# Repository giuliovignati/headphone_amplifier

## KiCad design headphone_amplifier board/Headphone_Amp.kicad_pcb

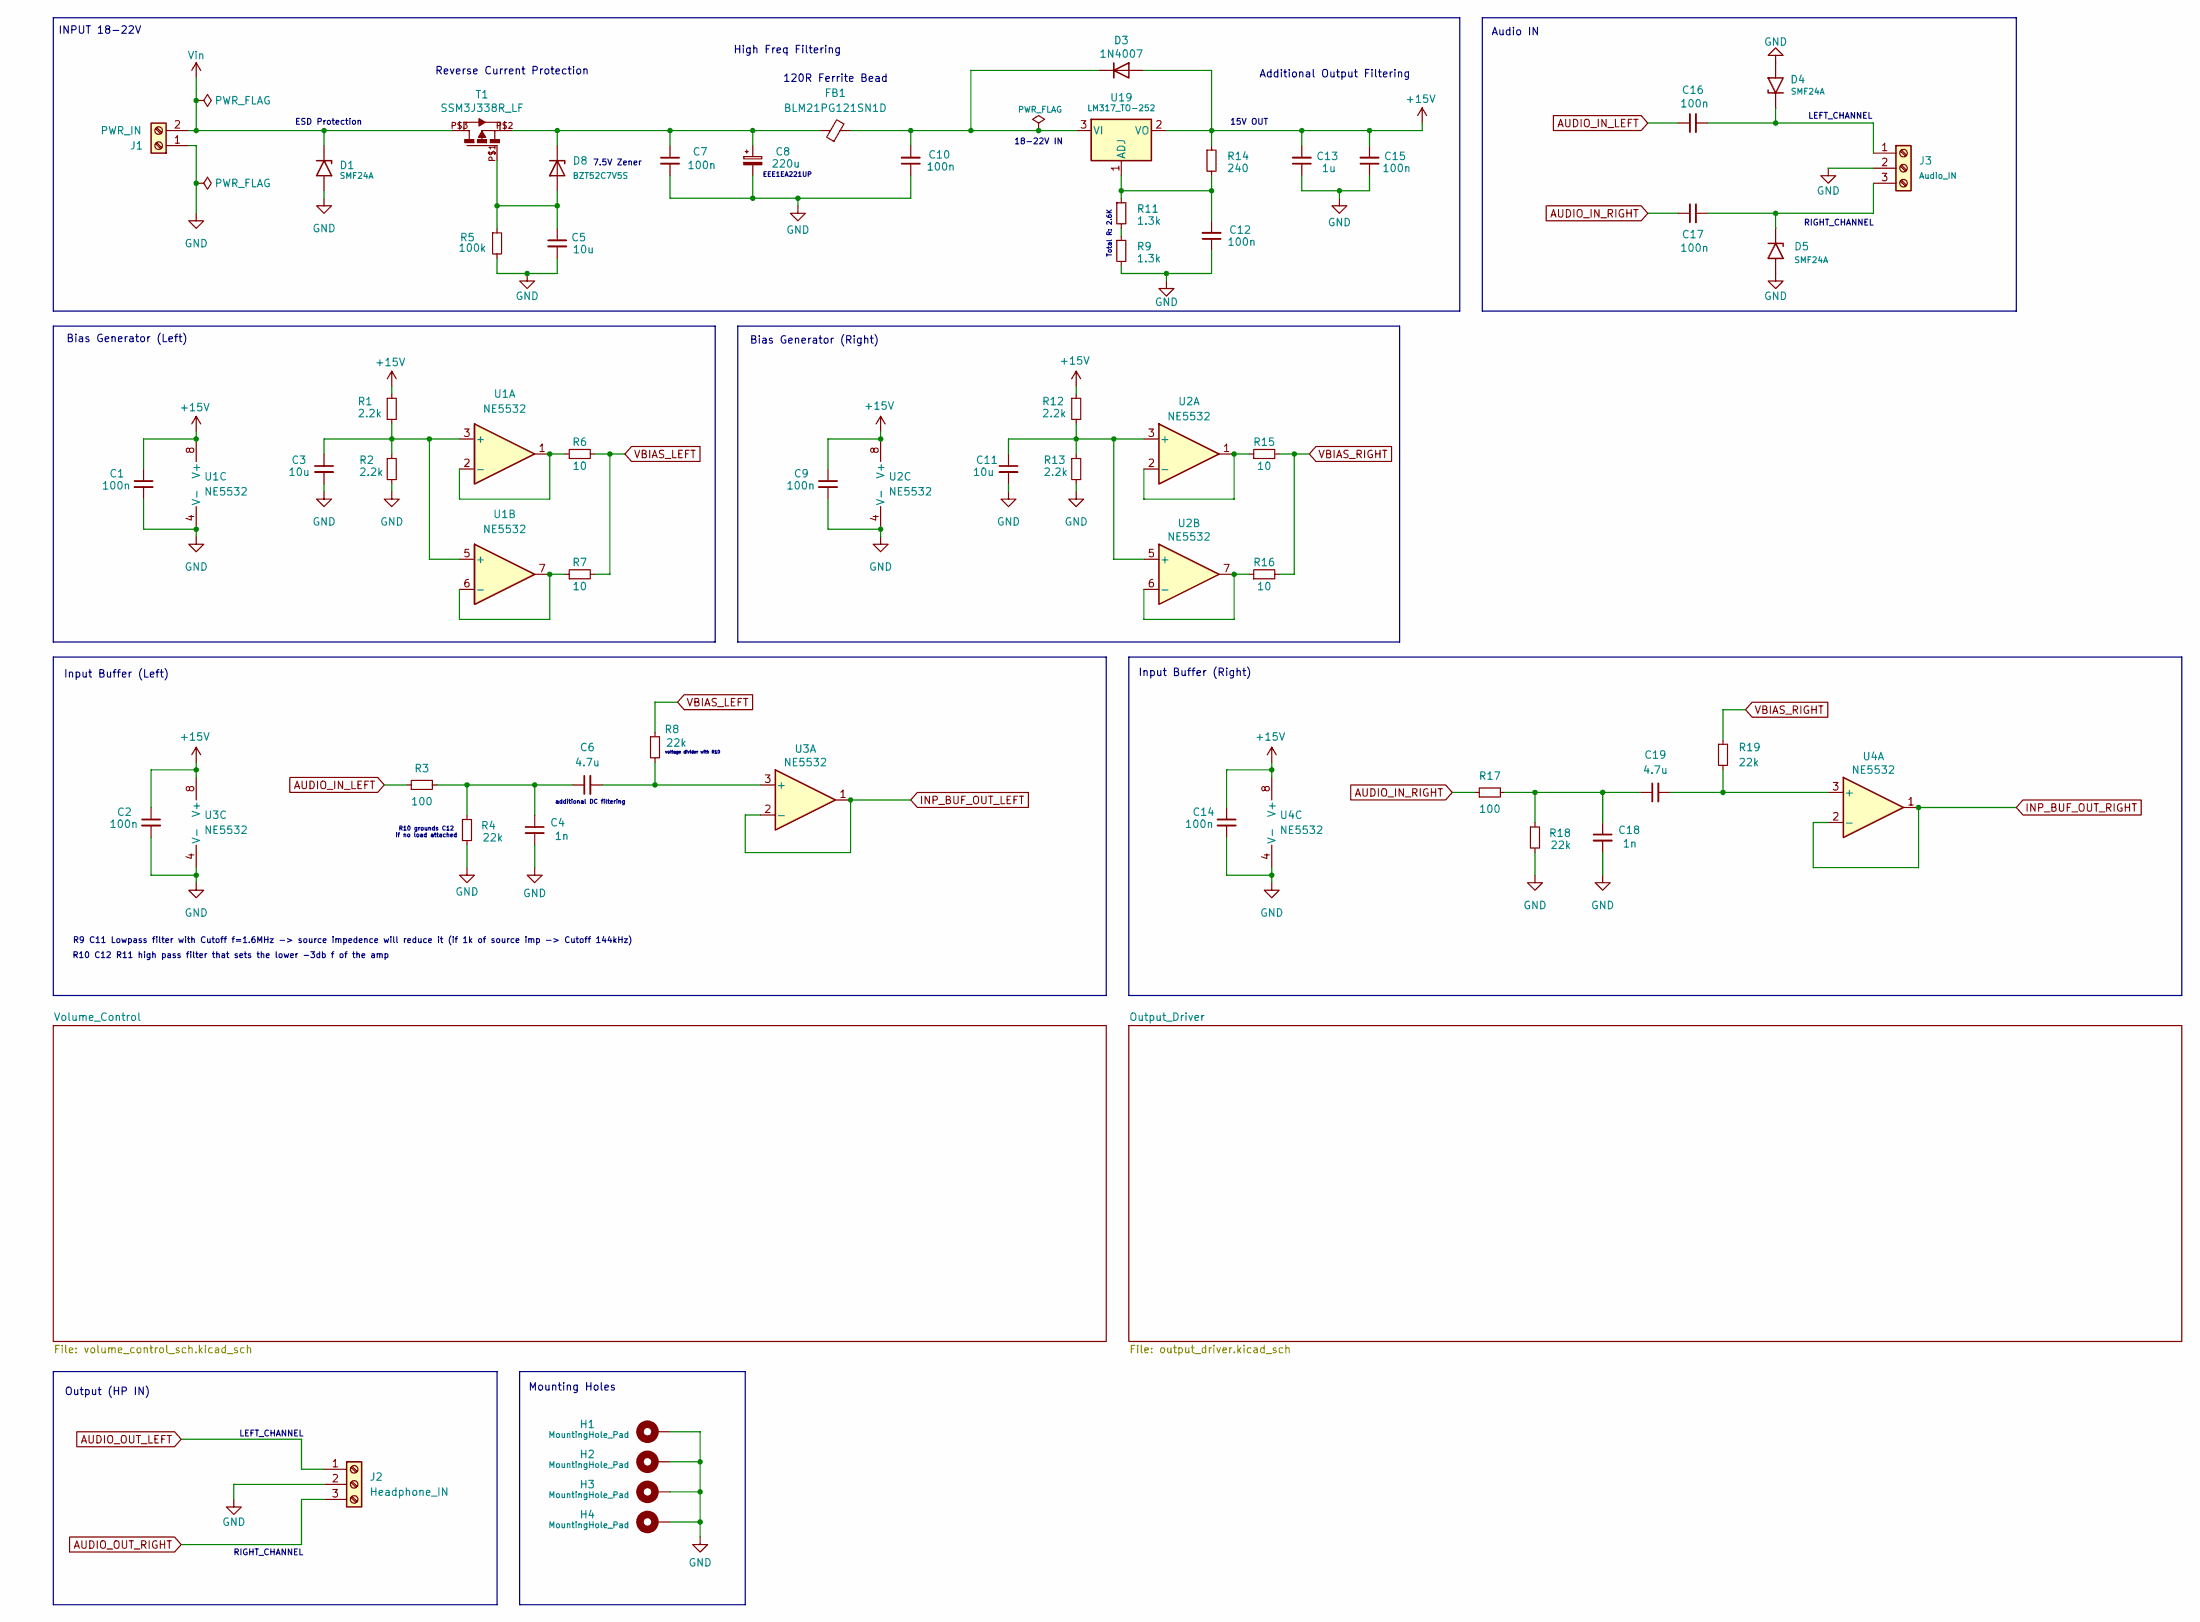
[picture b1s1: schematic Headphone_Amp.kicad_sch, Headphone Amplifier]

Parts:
C1, C2, C7, C9, C10, C12, C14, C15, C16, C17: 100n; C_0805_2012Metric_Pad1.18x1.45mm_HandSolder
C3, C5, C11: 10u; C_0805_2012Metric_Pad1.18x1.45mm_HandSolder
C4, C18: 1n; C_0805_2012Metric_Pad1.18x1.45mm_HandSolder
C6, C19: 4.7u; C_0805_2012Metric_Pad1.18x1.45mm_HandSolder
C8: 220u; EEE1EA221UP
C13: 1u; C_0805_2012Metric_Pad1.18x1.45mm_HandSolder
D1, D4, D5: SMF24A; D_SOD-123
D3: 1N4007; D_SMA
D8: BZT52C7V5S; D_SOD-123F
FB1: BLM21PG121SN1D; C_0805_2012Metric_Pad1.18x1.45mm_HandSolder
H1, H2, H3, H4: MountingHole_Pad; MountingHole_3.2mm_M3_Pad_Via
J1: PWR_IN; TerminalBlock_bornier-2_P5.08mm
J2: Headphone_IN; TerminalBlock_bornier-3_P5.08mm
J3: Audio_IN; TerminalBlock_bornier-3_P5.08mm
R1, R2, R12, R13: 2.2k; R_0805_2012Metric_Pad1.20x1.40mm_HandSolder
R3, R17: 100; R_0805_2012Metric_Pad1.20x1.40mm_HandSolder
R4, R8, R18, R19: 22k; R_0805_2012Metric_Pad1.20x1.40mm_HandSolder
R5: 100k; R_0805_2012Metric_Pad1.20x1.40mm_HandSolder
R6, R7, R15, R16: 10; R_0805_2012Metric_Pad1.20x1.40mm_HandSolder
R9, R11: 1.3k; R_0805_2012Metric_Pad1.20x1.40mm_HandSolder
R14: 240; R_0805_2012Metric_Pad1.20x1.40mm_HandSolder
T1: SSM3J338R_LF
U1, U2, U3, U4: NE5532; SOIC-8_3.9x4.9mm_P1.27mm
U19: LM317_TO-252; SOT-223

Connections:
+15V: C1.1, C2.1, C9.1, C13.2, C14.1, C15.2, D3.2 (A), R1.1, R12.1, R14.1, U1.8 (V+), U2.8 (V+), U3.8 (V+), U4.8 (V+), U19.2 (VO); also elsewhere on the board
AUDIO_IN_LEFT: C16.1, R3.1
AUDIO_IN_RIGHT: C17.1, R17.1
AUDIO_OUT_LEFT: J2.1; also elsewhere on the board
AUDIO_OUT_RIGHT: J2.3; also elsewhere on the board
GND: C1.2, C2.2, C3.2, C4.2, C5.2, C7.2, C8.2, C9.2, C10.1, C11.2, C12.1, C13.1, C14.2, C15.1, C18.2, D1.2 (A2), D4.2 (A2), D5.2 (A2), H1.1, H2.1, H3.1, H4.1, J1.1, J2.2, J3.2, R2.2, R4.2, R5.2, R9.2, R13.2, R18.2, U1.4 (V-), U2.4 (V-), U3.4 (V-), U4.4 (V-); also elsewhere on the board
INP_BUF_OUT_LEFT: U3.1, U3.2 (-); also elsewhere on the board
INP_BUF_OUT_RIGHT: U4.1, U4.2 (-); also elsewhere on the board
unnamed: C4.1, C6.1, R3.2, R4.1
unnamed: C18.1, C19.1, R17.2, R18.1
unnamed: C10.2, D3.1 (K), FB1.2, U19.3 (VI)
unnamed: C16.2, D4.1 (A1), J3.1
unnamed: C17.2, D5.1 (A1), J3.3
unnamed: C5.1, D8.2 (A), R5.1, T1.P$1
unnamed: C7.1, C8.1, D8.1 (K), FB1.1, T1.P$2
unnamed: R9.1, R11.2
unnamed: C3.1, R1.2, R2.1, U1.3 (+), U1.5 (+)
unnamed: R6.1, U1.1, U1.2 (-)
unnamed: R7.1, U1.6 (-), U1.7
unnamed: C11.1, R12.2, R13.1, U2.3 (+), U2.5 (+)
unnamed: R15.1, U2.1, U2.2 (-)
unnamed: R16.1, U2.6 (-), U2.7
unnamed: C6.2, R8.2, U3.3 (+)
unnamed: C19.2, R19.2, U4.3 (+)
unnamed: C12.2, R11.1, R14.2, U19.1 (ADJ)
VBIAS_LEFT: R6.2, R7.2, R8.1; also elsewhere on the board
VBIAS_RIGHT: R15.2, R16.2, R19.1; also elsewhere on the board
Vin: D1.1 (A1), J1.2, T1.P$3

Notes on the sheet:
Audio IN
120R Ferrite Bead
15V OUT
ESD Protection
7.5V Zener
R10 C12 R11 high pass filter that sets the lower -3db f of the amp
Total R: 2.6K
Bias Generator (Right)
Mounting Holes
Input Buffer (Right)
High Freq Filtering
Output (HP IN)
EEE1EA221UP
Reverse Current Protection
RIGHT_CHANNEL
Bias Generator (Left)
LEFT_CHANNEL
INPUT 18-22V
R10 grounds C12 if no load attached
18-22V IN
Additional Output Filtering
R9 C11 Lowpass filter with Cutoff f=1.6MHz -> source impedence will reduce it (if 1k of source imp -> Cutoff 144kHz)
Input Buffer (Left)
voltage divider with R10
additional DC filtering

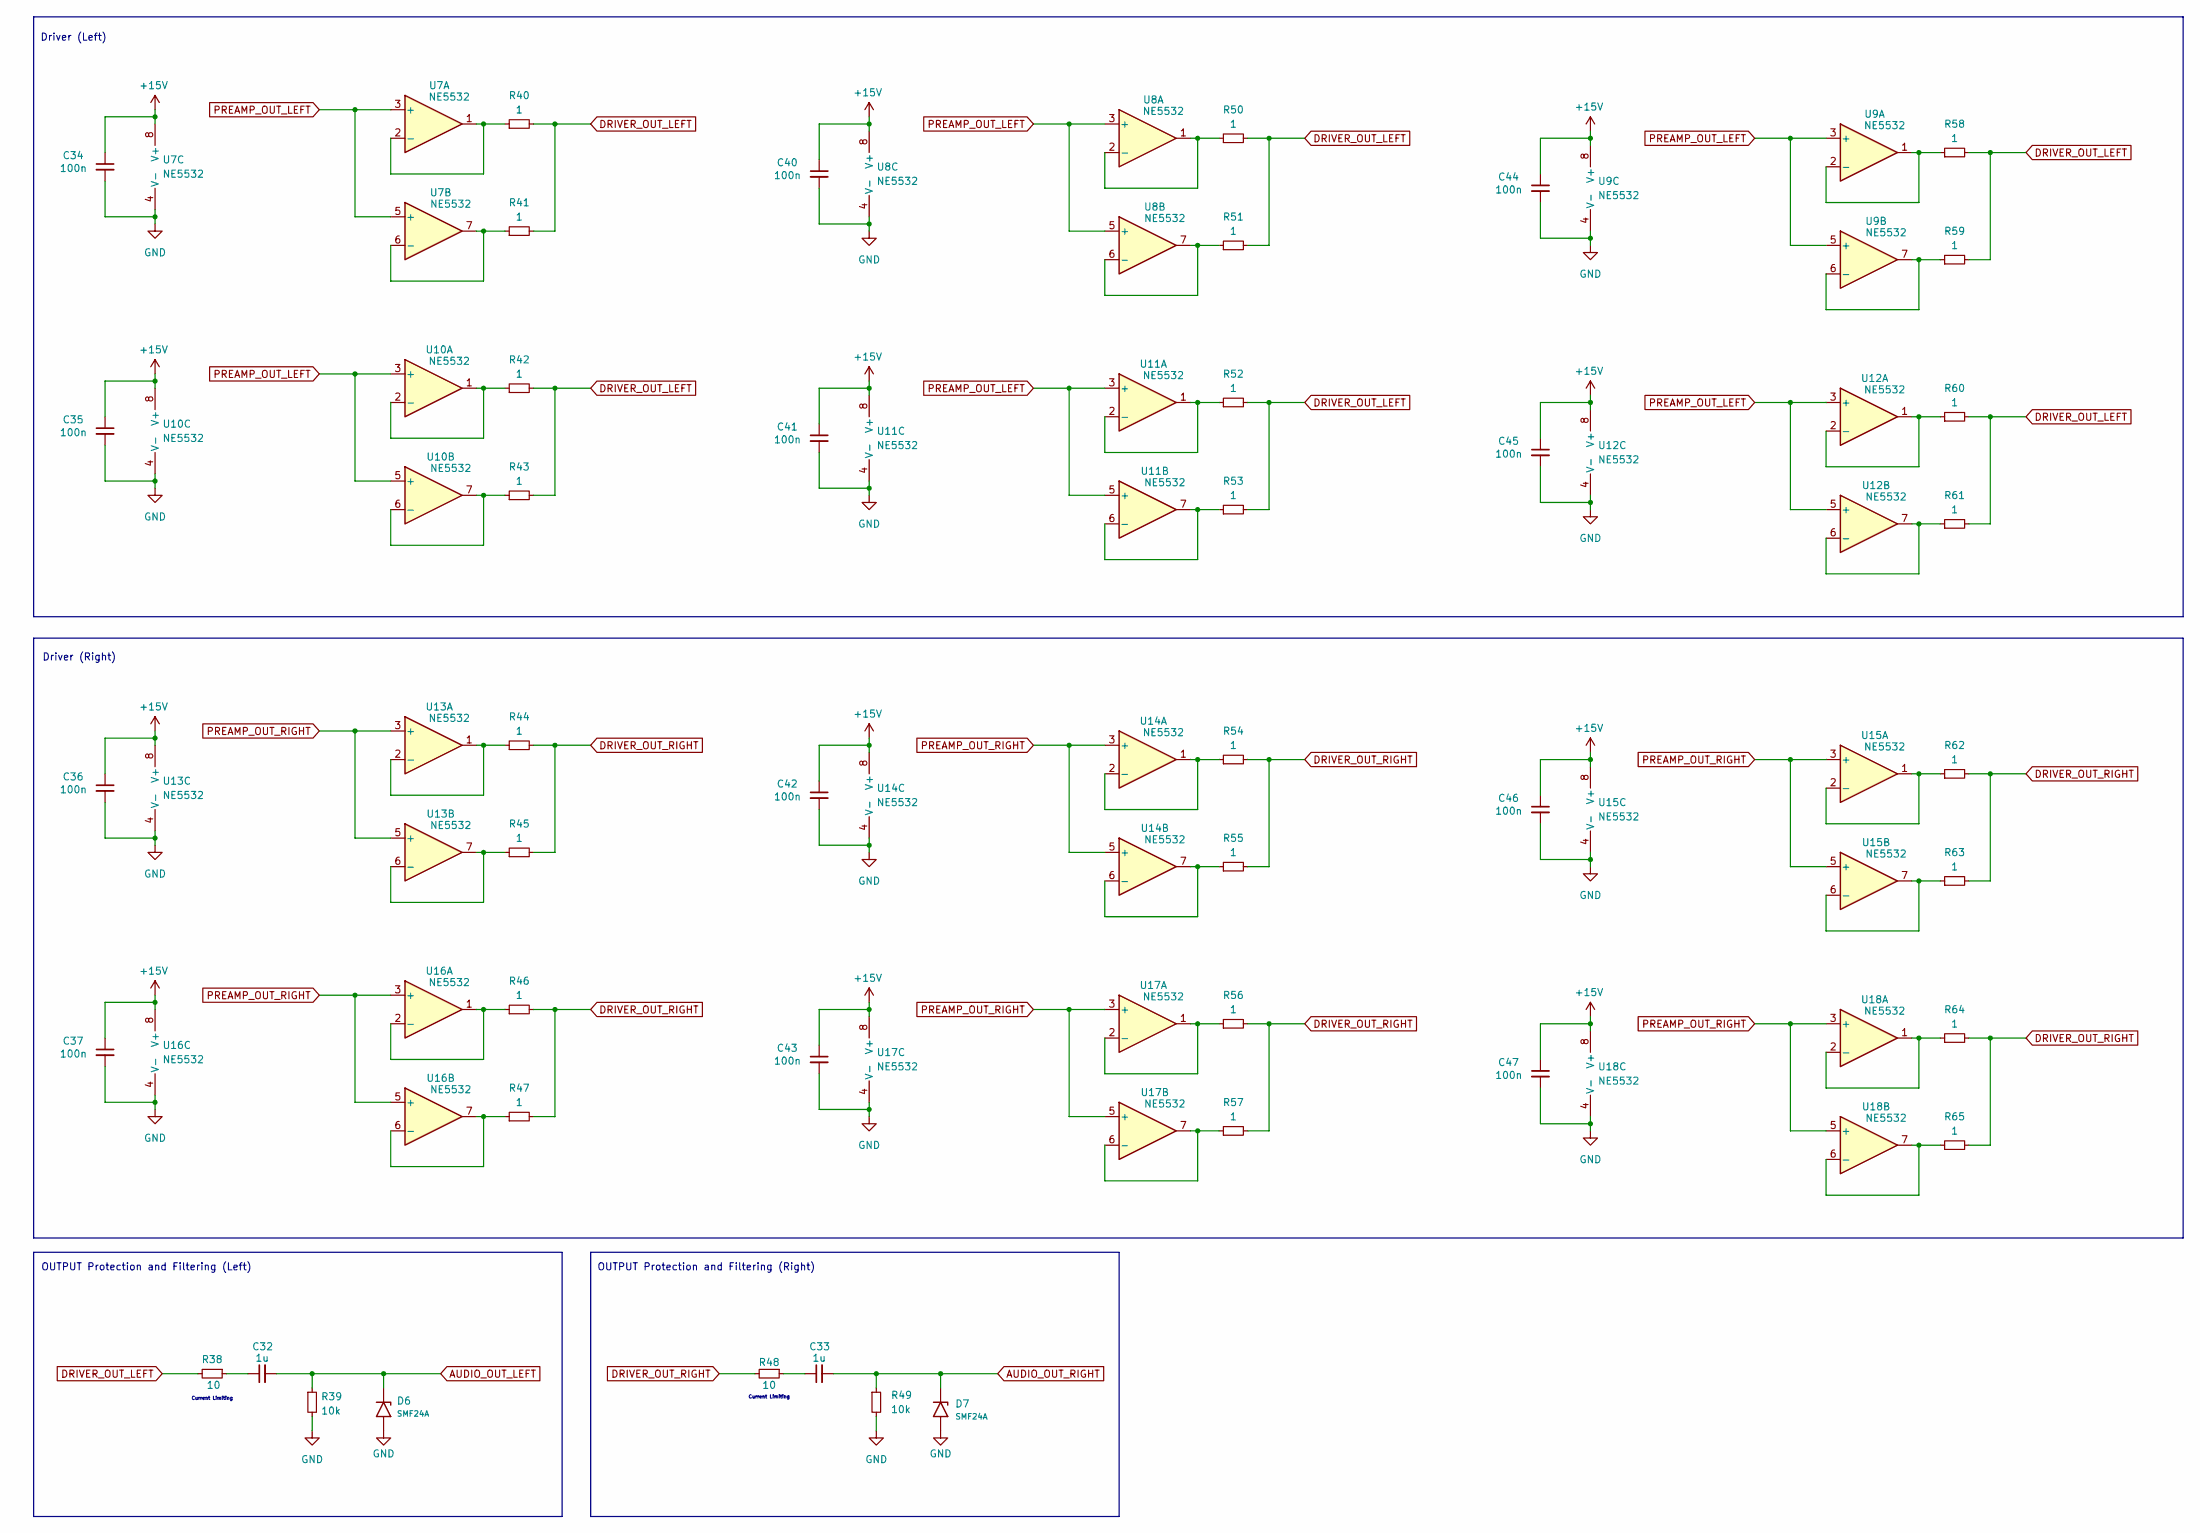
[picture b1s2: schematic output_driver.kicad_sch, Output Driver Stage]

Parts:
C32, C33: 1u; C_Rect_L18.0mm_W7.0mm_P15.00mm_FKS3_FKP3
C34, C35, C36, C37, C40, C41, C42, C43, C44, C45, C46, C47: 100n; C_0805_2012Metric_Pad1.18x1.45mm_HandSolder
D6, D7: SMF24A; D_SOD-123
R38, R48: 10; R_0805_2012Metric_Pad1.20x1.40mm_HandSolder
R39, R49: 10k; R_0805_2012Metric_Pad1.20x1.40mm_HandSolder
R40, R41, R42, R43, R44, R45, R46, R47, R50, R51, R52, R53, R54, R55, R56, R57, R58, R59, R60, R61, R62, R63, R64, R65: 1; R_0805_2012Metric_Pad1.20x1.40mm_HandSolder
U7, U8, U9, U10, U11, U12, U13, U14, U15, U16, U17, U18: NE5532; SOIC-8_3.9x4.9mm_P1.27mm

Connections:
+15V: C34.1, C35.1, C36.1, C37.1, C40.1, C41.1, C42.1, C43.1, C44.1, C45.1, C46.1, C47.1, U7.8 (V+), U8.8 (V+), U9.8 (V+), U10.8 (V+), U11.8 (V+), U12.8 (V+), U13.8 (V+), U14.8 (V+), U15.8 (V+), U16.8 (V+), U17.8 (V+), U18.8 (V+); also elsewhere on the board
AUDIO_OUT_LEFT: C32.2, D6.1 (A1), R39.1; also elsewhere on the board
AUDIO_OUT_RIGHT: C33.2, D7.1 (A1), R49.1; also elsewhere on the board
DRIVER_OUT_LEFT: R38.2, R40.2, R41.2, R42.2, R43.2, R50.2, R51.2, R52.2, R53.2, R58.2, R59.2, R60.2, R61.2
DRIVER_OUT_RIGHT: R44.2, R45.2, R46.2, R47.2, R48.2, R54.2, R55.2, R56.2, R57.2, R62.2, R63.2, R64.2, R65.2
GND: C34.2, C35.2, C36.2, C37.2, C40.2, C41.2, C42.2, C43.2, C44.2, C45.2, C46.2, C47.2, D6.2 (A2), D7.2 (A2), R39.2, R49.2, U7.4 (V-), U8.4 (V-), U9.4 (V-), U10.4 (V-), U11.4 (V-), U12.4 (V-), U13.4 (V-), U14.4 (V-), U15.4 (V-), U16.4 (V-), U17.4 (V-), U18.4 (V-); also elsewhere on the board
unnamed: C32.1, R38.1
unnamed: C33.1, R48.1
unnamed: R40.1, U7.1, U7.2 (-)
unnamed: R41.1, U7.6 (-), U7.7
unnamed: R50.1, U8.1, U8.2 (-)
unnamed: R51.1, U8.6 (-), U8.7
unnamed: R58.1, U9.1, U9.2 (-)
unnamed: R59.1, U9.6 (-), U9.7
unnamed: R42.1, U10.1, U10.2 (-)
unnamed: R43.1, U10.6 (-), U10.7
unnamed: R52.1, U11.1, U11.2 (-)
unnamed: R53.1, U11.6 (-), U11.7
unnamed: R60.1, U12.1, U12.2 (-)
unnamed: R61.1, U12.6 (-), U12.7
unnamed: R44.1, U13.1, U13.2 (-)
unnamed: R45.1, U13.6 (-), U13.7
unnamed: R54.1, U14.1, U14.2 (-)
unnamed: R55.1, U14.6 (-), U14.7
unnamed: R62.1, U15.1, U15.2 (-)
unnamed: R63.1, U15.6 (-), U15.7
unnamed: R46.1, U16.1, U16.2 (-)
unnamed: R47.1, U16.6 (-), U16.7
unnamed: R56.1, U17.1, U17.2 (-)
unnamed: R57.1, U17.6 (-), U17.7
unnamed: R64.1, U18.1, U18.2 (-)
unnamed: R65.1, U18.6 (-), U18.7
PREAMP_OUT_LEFT: U7.3 (+), U7.5 (+), U8.3 (+), U8.5 (+), U9.3 (+), U9.5 (+), U10.3 (+), U10.5 (+), U11.3 (+), U11.5 (+), U12.3 (+), U12.5 (+); also elsewhere on the board
PREAMP_OUT_RIGHT: U13.3 (+), U13.5 (+), U14.3 (+), U14.5 (+), U15.3 (+), U15.5 (+), U16.3 (+), U16.5 (+), U17.3 (+), U17.5 (+), U18.3 (+), U18.5 (+); also elsewhere on the board

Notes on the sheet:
Driver (Left)
Current Limiting
Driver (Right)
OUTPUT Protection and Filtering (Right)
OUTPUT Protection and Filtering (Left)

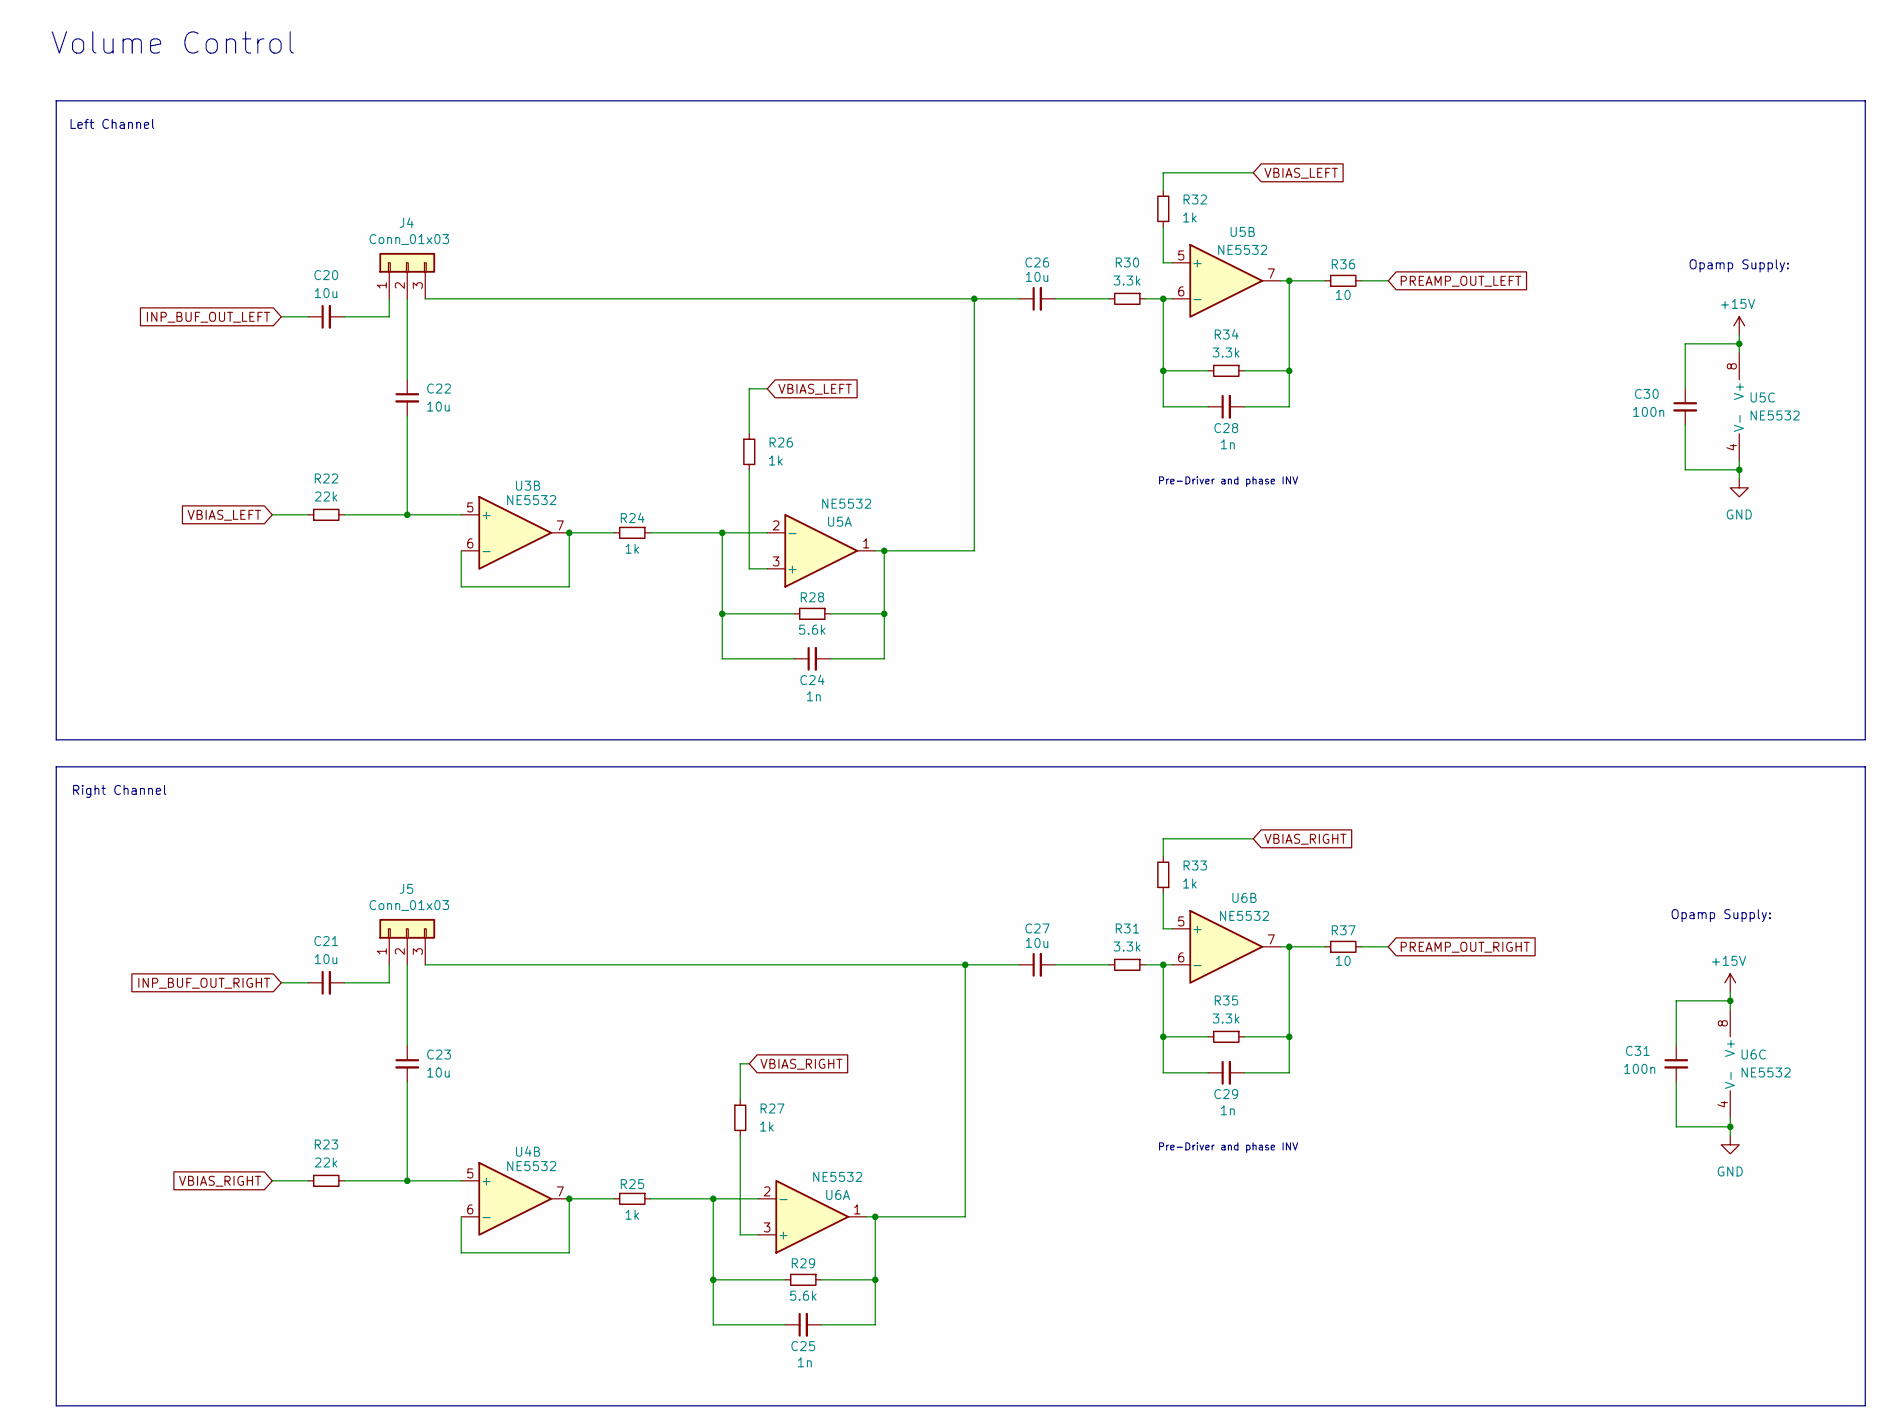
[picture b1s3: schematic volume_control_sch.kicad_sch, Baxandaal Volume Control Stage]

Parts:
C20, C21, C22, C23, C26, C27: 10u; C_0805_2012Metric_Pad1.18x1.45mm_HandSolder
C24, C25, C28, C29: 1n; C_0805_2012Metric_Pad1.18x1.45mm_HandSolder
C30, C31: 100n; C_0805_2012Metric_Pad1.18x1.45mm_HandSolder
J4, J5: Conn_01x03; PinHeader_1x03_P2.54mm_Vertical
R22, R23: 22k; R_0805_2012Metric_Pad1.20x1.40mm_HandSolder
R24, R25, R26, R27, R32, R33: 1k; R_0805_2012Metric_Pad1.20x1.40mm_HandSolder
R28, R29: 5.6k; R_0805_2012Metric_Pad1.20x1.40mm_HandSolder
R30, R31, R34, R35: 3.3k; R_0805_2012Metric_Pad1.20x1.40mm_HandSolder
R36, R37: 10; R_0805_2012Metric_Pad1.20x1.40mm_HandSolder
U3, U4, U5, U6: NE5532; SOIC-8_3.9x4.9mm_P1.27mm

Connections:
+15V: C30.1, C31.1, U5.8 (V+), U6.8 (V+); also elsewhere on the board
GND: C30.2, C31.2, U5.4 (V-), U6.4 (V-); also elsewhere on the board
INP_BUF_OUT_LEFT: C20.1; also elsewhere on the board
INP_BUF_OUT_RIGHT: C21.1; also elsewhere on the board
unnamed: C26.2, R30.2
unnamed: C27.2, R31.2
unnamed: C28.2, R34.1, R36.1, U5.7
unnamed: C29.2, R35.1, R37.1, U6.7
unnamed: C20.2, J4.1
unnamed: C22.1, J4.2
unnamed: C24.2, C26.1, J4.3, R28.1, U5.1
unnamed: C21.2, J5.1
unnamed: C23.1, J5.2
unnamed: C25.2, C27.1, J5.3, R29.1, U6.1
unnamed: C22.2, R22.2, U3.5 (+)
unnamed: R24.2, U3.6 (-), U3.7
unnamed: C23.2, R23.2, U4.5 (+)
unnamed: R25.2, U4.6 (-), U4.7
unnamed: R26.2, U5.3 (+)
unnamed: C24.1, R24.1, R28.2, U5.2 (-)
unnamed: R32.1, U5.5 (+)
unnamed: C28.1, R30.1, R34.2, U5.6 (-)
unnamed: R27.2, U6.3 (+)
unnamed: C25.1, R25.1, R29.2, U6.2 (-)
unnamed: R33.1, U6.5 (+)
unnamed: C29.1, R31.1, R35.2, U6.6 (-)
PREAMP_OUT_LEFT: R36.2; also elsewhere on the board
PREAMP_OUT_RIGHT: R37.2; also elsewhere on the board
VBIAS_LEFT: R22.1, R26.1, R32.2; also elsewhere on the board
VBIAS_RIGHT: R23.1, R27.1, R33.2; also elsewhere on the board

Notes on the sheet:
Left Channel
Opamp Supply:
Right Channel
Pre-Driver and phase INV
Volume Control

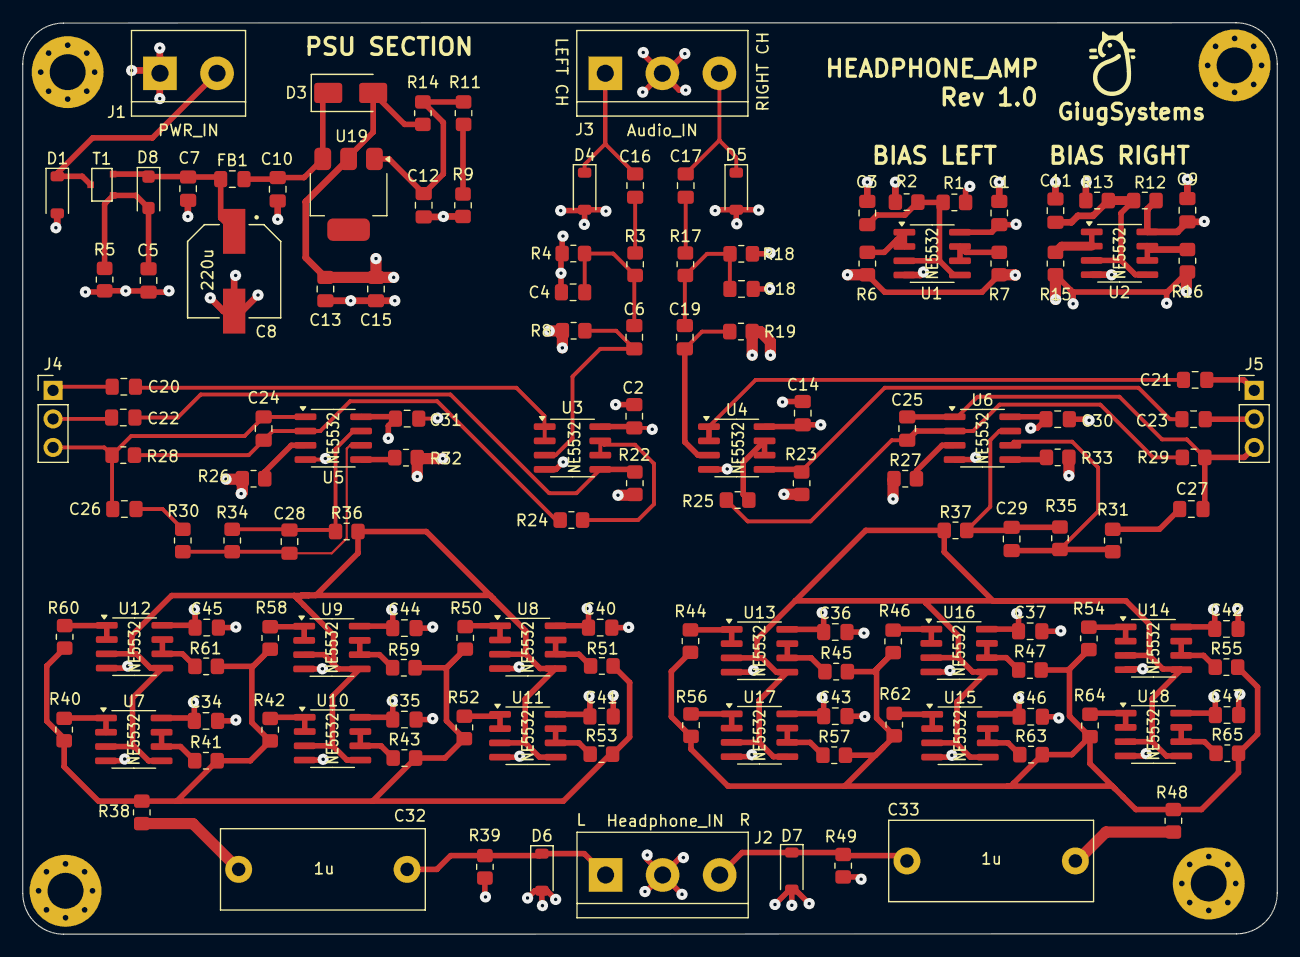
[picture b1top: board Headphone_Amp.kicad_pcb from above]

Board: 4 copper layers, 111.7 x 81.2 mm, 144 parts (0 on the bottom side), 80 nets.

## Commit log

2024-12-22 first ver
2024-12-30 Bug Fix
2025-02-15 updated routing
2025-02-23 revisited bias plane
